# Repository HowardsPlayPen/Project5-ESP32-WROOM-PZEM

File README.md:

# Project 5: ESP32WROOM + some SMD soldering

So far, all my projects had involved modules for each component, such as using an ESP32-CAM, but I wanted to move to use more compact components - such as the ESP32-S2. The camera on the ESP32-CAM is amazing and simple to use - but for most of the projects I wanted to build having more GPIO pins available seemed like a better option.

At this point a friend sent me the following [link](https://twitter.com/i/status/1598419769077952512) showing an amazing PCB that was not much thicker than the PCB board but with a wonderul TFT screen built in

The twitter feed included a link to where you can buy the TFT on [AliExpress](https://www.aliexpress.com/item/1005003768946439.html)

Specs: 240*280 RGB Build-in ST7789 Driver Serial IPS Display

Note: this is **WAY** better than the SSD1306 I have been using which is a 0.96' screen 128x64 single colour screen

I wanted to try out these screens but I haven't soldered FPC cables before and so I bought several of these and one module that breaks out the wires into standard 2.54 mm pins. This way I could test the board to know it drives the panel ok before worrying about the FPC side

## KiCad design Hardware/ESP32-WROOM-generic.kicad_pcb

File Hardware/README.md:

# Project5-ESP32-WROOM

Using an ESP32-WROOM + RFM69HW + PZEM + pinouts for a few different LED screens.

## Aim

Test out various different circuits - including touch buttons connected to ESP32 pins (I read that they could work as capacitative buttons)

It includes a connector for PZEM - i.e. ability to monitor 240V power use.

### PZEM v3
I bought my PZEM from Aliexpress but they are available everywhere, eg. [see here](https://esphome.io/components/sensor/pzemac.html)

## NOTE about OLED screen / board

> Note: this board does not connect BLK to 3V as the documentation said it was optional. This PCB works for the ST7789V2 boards that I have, but does not work for a newer ST7789V3 board where it **NEEDS**  BLK to be connected to 3V.

### Kicad Rendering of the PCB

### Kicad view of the PCB

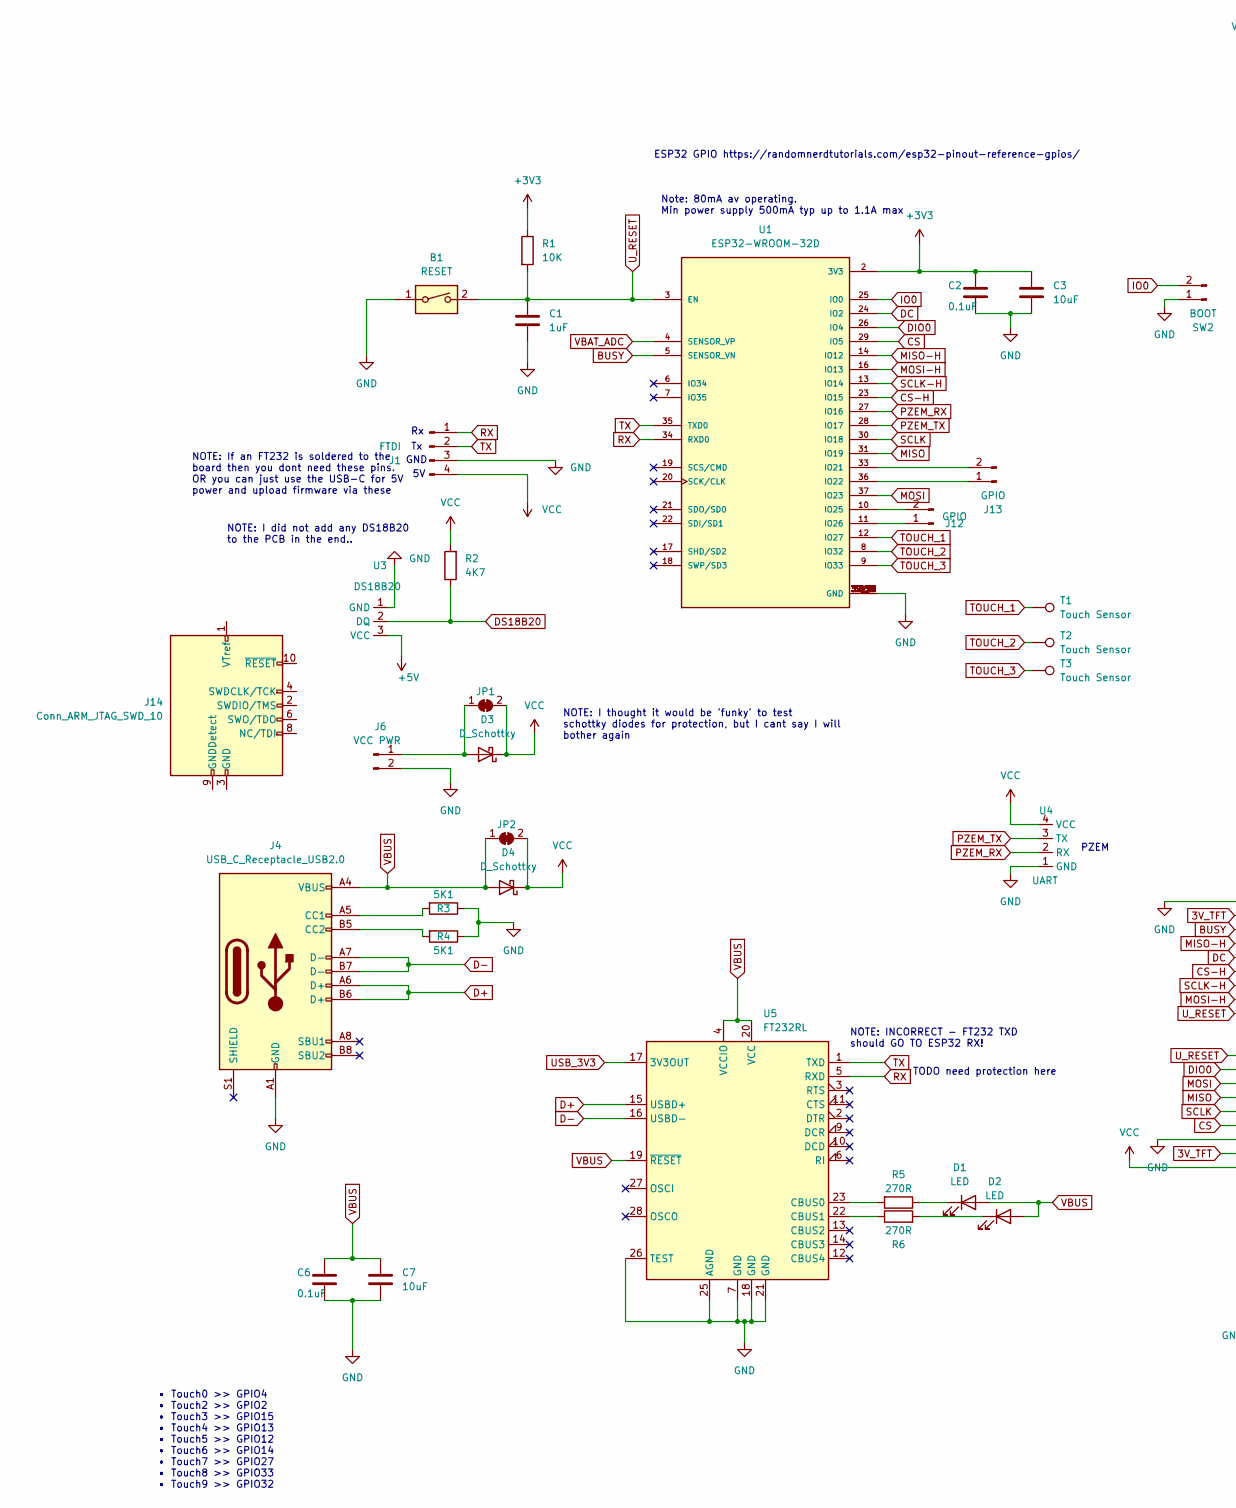
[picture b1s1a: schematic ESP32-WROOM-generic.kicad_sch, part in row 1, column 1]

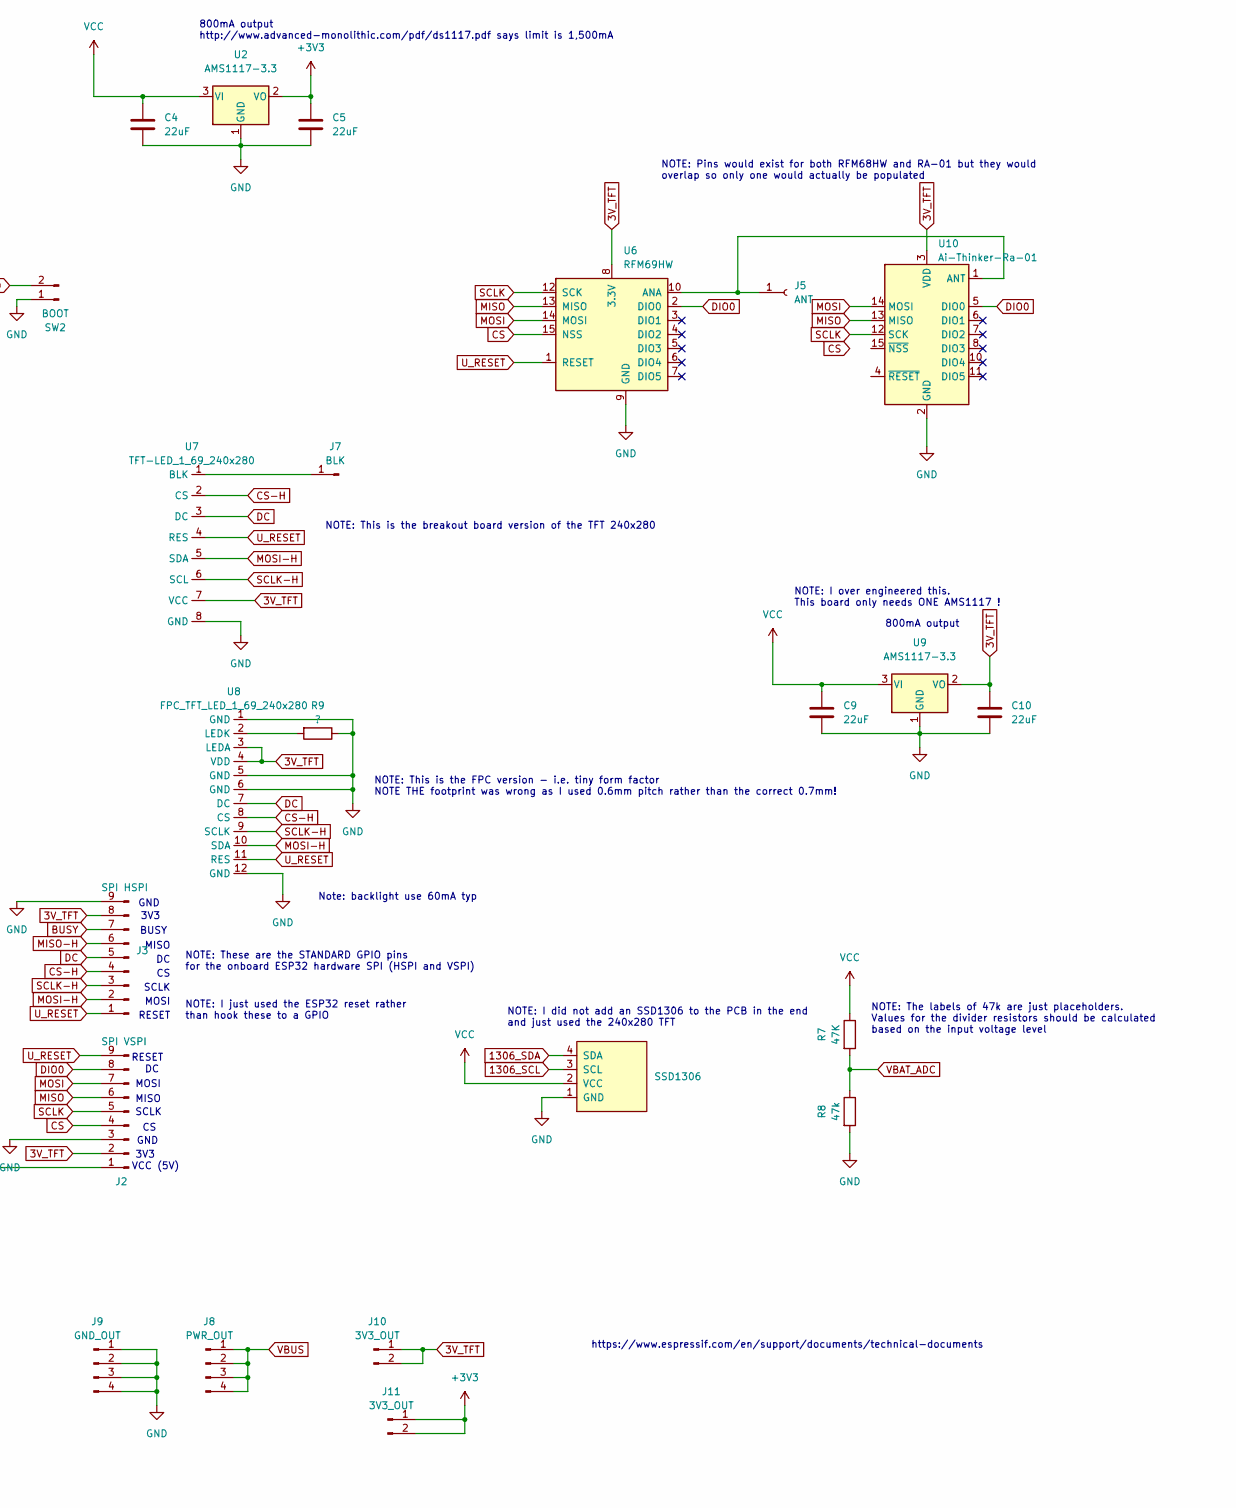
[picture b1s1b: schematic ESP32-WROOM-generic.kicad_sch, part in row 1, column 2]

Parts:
B1: RESET; SW_DIP_SPSTx01_Slide_6.7x4.1mm_W8.61mm_P2.54mm_LowProfile
Brd1: SSD1306; 128x64OLED
C1: 1uF; C_0504_1310Metric_Pad0.83x1.28mm_HandSolder
C2, C6: 0.1uF; C_0504_1310Metric_Pad0.83x1.28mm_HandSolder
C3, C7: 10uF; C_0504_1310Metric_Pad0.83x1.28mm_HandSolder
C4, C5, C9, C10: 22uF; C_0504_1310Metric_Pad0.83x1.28mm_HandSolder
D1, D2: LED; LED_1206_3216Metric_Pad1.42x1.75mm_HandSolder
D3, D4: D_Schottky; D_MELF
J1: FTDI; JST_EH_B4B-EH-A_1x04_P2.50mm_Vertical
J2: SPI VSPI; JST_EH_B9B-EH-A_1x09_P2.50mm_Vertical
J3: SPI HSPI; JST_EH_B9B-EH-A_1x09_P2.50mm_Vertical
J4: USB_C_Receptacle_USB2.0; USB_C_Receptacle_HRO_TYPE-C-31-M-12
J5: ANT; Pin_D1.0mm_L10.0mm
J6: VCC PWR; JST_EH_B2B-EH-A_1x02_P2.50mm_Vertical
J7: BLK; TestPoint_Plated_Hole_D2.0mm
J8: PWR_OUT; JST_EH_B4B-EH-A_1x04_P2.50mm_Vertical
J9: GND_OUT; JST_EH_B4B-EH-A_1x04_P2.50mm_Vertical
J10, J11: 3V3_OUT; JST_EH_B2B-EH-A_1x02_P2.50mm_Vertical
J12, J13: GPIO; JST_EH_B2B-EH-A_1x02_P2.50mm_Vertical
J14: Conn_ARM_JTAG_SWD_10
JP1, JP2: SolderJumper_2_Bridged; SolderJumper-2_P1.3mm_Bridged_Pad1.0x1.5mm
R1: 10K; R_1206_3216Metric_Pad1.30x1.75mm_HandSolder
R2: 4K7; R_1206_3216Metric_Pad1.30x1.75mm_HandSolder
R3, R4: 5K1; R_1206_3216Metric_Pad1.30x1.75mm_HandSolder
R5, R6: 270R; R_1206_3216Metric_Pad1.30x1.75mm_HandSolder
R7: 47K; R_1206_3216Metric_Pad1.30x1.75mm_HandSolder
R8: 47k; R_1206_3216Metric_Pad1.30x1.75mm_HandSolder
R9: ?; R_1206_3216Metric_Pad1.30x1.75mm_HandSolder
SW2: BOOT; JST_EH_B2B-EH-A_1x02_P2.50mm_Vertical
T1, T2, T3: Touch Sensor; TestPoint_Pad_D4.0mm
U1: ESP32-WROOM-32D; MODULE_ESP32-WROOM-32D; PARTREV 1.9
U2, U9: AMS1117-3.3; SOT-223-3_TabPin2
U3: DS18B20; JST_NV_B03P-NV_1x03_P5.00mm_Vertical
U4: UART; JST_EH_B4B-EH-A_1x04_P2.50mm_Vertical
U5: FT232RL; SSOP-28_5.3x10.2mm_P0.65mm
U6: RFM69HW; HOPERF_RFM69HW
U7: TFT-LED_1_69_240x280
U8: FPC_TFT_LED_1_69_240x280; FPC_TFT_1_69_240x280
U10: Ai-Thinker-Ra-01; Ai-Thinker-Ra-01-LoRa

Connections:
3V_TFT: C10.1, J2.2, J3.8, J10.1, J10.2, U6.8 (3.3V), U7.7 (VCC), U8.3 (LEDA), U8.4 (VDD), U9.2 (VO), U10.3 (VDD)
+3V3: C2.1, C3.1, C5.1, J11.1, J11.2, R1.1, U1.2 (3V3), U2.2 (VO)
BUSY: J3.7, U1.5 (SENSOR_VN)
CS: J2.4, U1.29 (IO5), U6.15 (NSS)
CS-H: J3.4, U1.23 (IO15), U7.2 (CS), U8.8 (CS)
D+: J4.A6 (D+), J4.B6 (D+), U5.15 (USBD+)
D-: J4.A7 (D-), J4.B7 (D-), U5.16 (USBD-)
DC: J3.5, U1.24 (IO2), U7.3 (DC), U8.7 (DC)
DIO0: J2.8, U1.26 (IO4), U6.2 (DIO0), U10.5 (DIO0)
GND: B1.1, Brd1.1 (GND), C1.2, C2.2, C3.2, C4.2, C5.2, C6.2, C7.2, C9.2, C10.2, J1.3, J2.3, J3.9, J4.A1 (GND), J4.A12 (GND), J4.B1 (GND), J4.B12 (GND), J6.2, J9.1, J9.2, J9.3, J9.4, R3.1, R4.1, R8.2, R9.1, SW2.1, U1.1 (GND), U1.15 (GND), U1.38 (GND), U1.39_1 (GND), U1.39_2 (GND), U1.39_3 (GND), U1.39_4 (GND), U1.39_5 (GND), U1.39_6 (GND), U1.39_7 (GND), U1.39_8 (GND), U1.39_9 (GND), U1.39_10 (GND), U1.39_11 (GND), U1.39_12 (GND), U1.39_13 (GND), U1.39_14 (GND), U1.39_15 (GND), U1.39_16 (GND), U1.39_17 (GND), U1.39_18 (GND), U1.39_19 (GND), U1.39_20 (GND), U1.39_21 (GND), U2.1 (GND), U3.1 (GND), U4.1 (GND), U5.7 (GND), U5.18 (GND), U5.21 (GND), U5.25 (AGND), U5.26 (TEST), U6.9 (GND), U6.11 (GND), U7.8 (GND), U8.1 (GND), U8.5 (GND), U8.6 (GND), U8.12 (GND), U9.1 (GND), U10.2 (GND), U10.9 (GND), U10.16 (GND); also elsewhere on the board
IO0: SW2.2, U1.25 (IO0)
MISO: J2.6, U1.31 (IO19), U6.13 (MISO), U10.13 (MISO)
MISO-H: J3.6, U1.14 (IO12)
MOSI: J2.7, U1.37 (IO23), U6.14 (MOSI), U10.14 (MOSI)
MOSI-H: J3.2, U1.16 (IO13), U7.5 (SDA), U8.10 (SDA)
unnamed: D1.1 (K), R5.1
unnamed: D2.1 (K), R6.2
unnamed: D3.2 (A), J6.1, JP1.1 (A)
unnamed: J4.A5 (CC1), R3.2
unnamed: J4.B5 (CC2), R4.2
unnamed: J5.1, U6.10 (ANA), U10.1 (ANT)
unnamed: J7.1, U7.1 (BLK)
unnamed: J12.1, U1.11 (IO26)
unnamed: J12.2, U1.10 (IO25)
unnamed: J13.1, U1.36 (IO22)
unnamed: J13.2, U1.33 (IO21)
unnamed: J14.3 (GND), J14.5 (GND)
unnamed: R2.1, U3.2 (DQ)
unnamed: R5.2, U5.23 (CBUS0)
unnamed: R6.1, U5.22 (CBUS1)
unnamed: R9.2, U8.2 (LEDK)
PZEM_RX: U1.27 (IO16), U4.2 (RX)
PZEM_TX: U1.28 (IO17), U4.3 (TX)
RX: J1.1, U1.34 (RXD0), U5.5 (RXD)
SCLK: J2.5, U1.30 (IO18), U6.12 (SCK), U10.12 (SCK)
SCLK-H: J3.3, U1.13 (IO14), U7.6 (SCL), U8.9 (SCLK)
TOUCH_1: T1.1, U1.12 (IO27)
TOUCH_2: T2.1, U1.8 (IO32)
TOUCH_3: T3.1, U1.9 (IO33)
TX: J1.2, U1.35 (TXD0), U5.1 (TXD)
USB_3V3: U5.17 (3V3OUT)
U_RESET: B1.2, C1.1, J2.9, J3.1, R1.2, U1.3 (EN), U6.1 (RESET), U7.4 (RES), U8.11 (RES)
VBAT_ADC: R7.2, R8.1, U1.4 (SENSOR_VP)
VBUS: C6.1, C7.1, D1.2 (A), D2.2 (A), D4.2 (A), J4.A4 (VBUS), J4.A9 (VBUS), J4.B4 (VBUS), J4.B9 (VBUS), J8.1, J8.2, J8.3, J8.4, JP2.1 (A), U5.4 (VCCIO), U5.19 (~RESET), U5.20 (VCC); also elsewhere on the board
VCC: Brd1.2 (VCC), C4.1, C9.1, D3.1 (K), D4.1 (K), J1.4, J2.1, JP1.2 (B), JP2.2 (B), R2.2, R7.1, U2.3 (VI), U4.4 (VCC), U9.3 (VI)

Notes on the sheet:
RESET
NOTE: I over engineered this. This board only needs ONE AMS1117 !
Note: backlight use 60mA typ
NOTE: If an FT232 is soldered to the board then you dont need these pins. OR you can just use the USB-C for 5V power and upload firmware via these
NOTE: This is the FPC version - i.e. tiny form factor NOTE THE footprint was wrong as I used 0.6mm pitch rather than the correct 0.7mm!
NOTE: The labels of 47k are just placeholders. Values for the divider resistors should be calculated based on the input voltage level
NOTE: These are the STANDARD GPIO pins for the onboard ESP32 hardware SPI (HSPI and VSPI)
NOTE: I did not add any DS18B20 to the PCB in the end..
VCC (5V)
MOSI
ESP32 GPIO https://randomnerdtutorials.com/esp32-pinout-reference-gpios/
• Touch0 >> GPIO4 • Touch2 >> GPIO2 • Touch3 >> GPIO15 • Touch4 >> GPIO13 • Touch5 >> GPIO12 • Touch6 >> GPIO14 • Touch7 >> GPIO27 • Touch8 >> GPIO33 • Touch9 >> GPIO32
MISO
800mA output http://www.advanced-monolithic.com/pdf/ds1117.pdf says limit is 1,500mA
GND
3V3
TODO need protection here
NOTE: I thought it would be 'funky' to test schottky diodes for protection, but I cant say I will bother again
NOTE: Pins would exist for both RFM68HW and RA-01 but they would overlap so only one would actually be populated
800mA output
SCLK
NOTE: I did not add an SSD1306 to the PCB in the end and just used the 240x280 TFT
NOTE: INCORRECT - FT232 TXD should GO TO ESP32 RX!
NOTE: This is the breakout board version of the TFT 240x280
PZEM
Note: 80mA av operating. Min power supply 500mA typ up to 1.1A max
https://www.espressif.com/en/support/documents/technical-documents
NOTE: I just used the ESP32 reset rather than hook these to a GPIO
BUSY

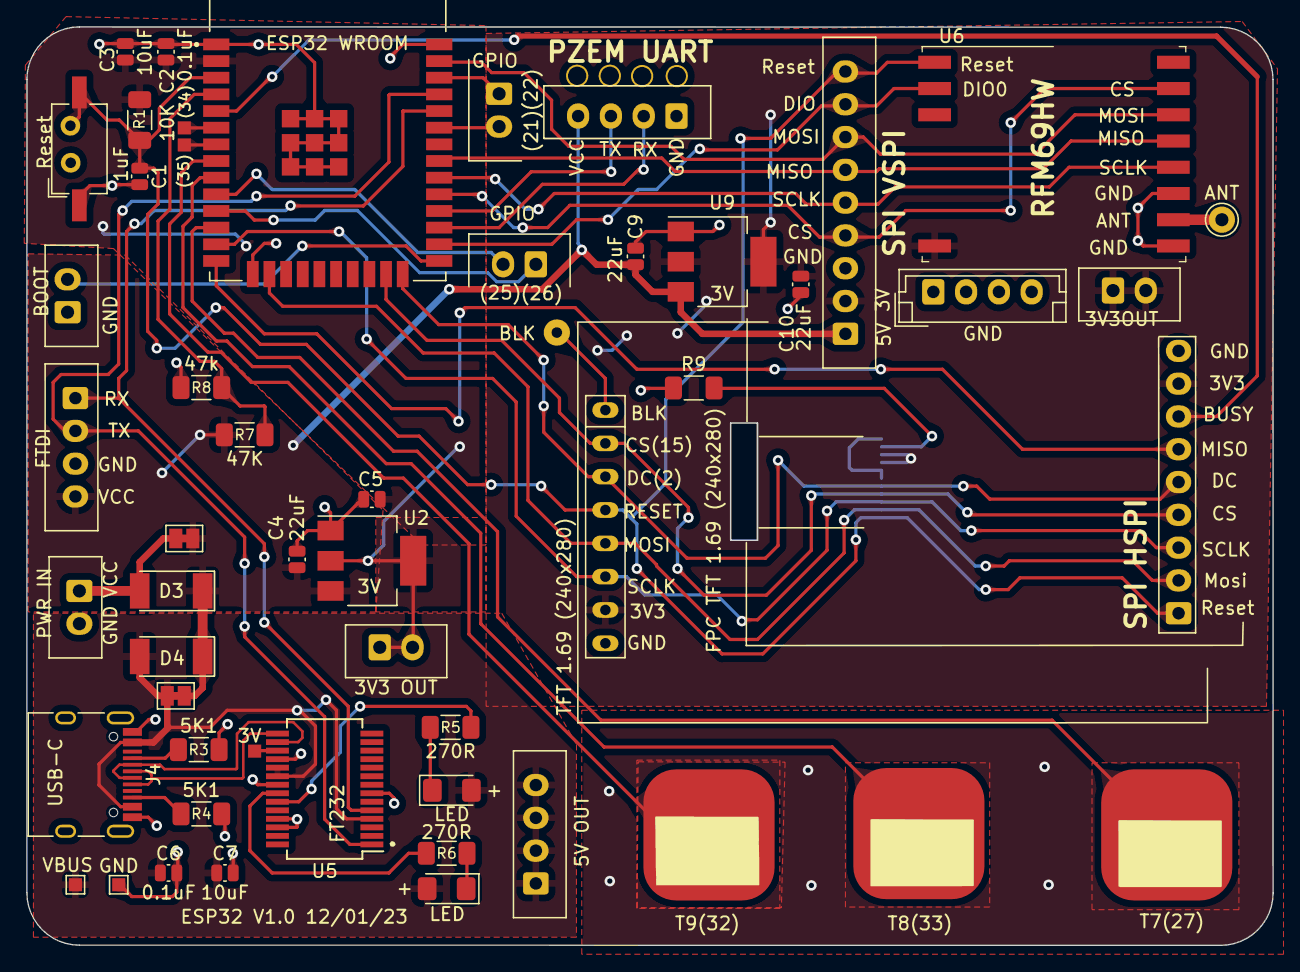
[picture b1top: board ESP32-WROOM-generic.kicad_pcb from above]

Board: 2 copper layers, 95.0 x 70.0 mm, 51 parts (0 on the bottom side), 42 nets.

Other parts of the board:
GND: TestPoint_Pad_1.0x1.0mm
VBUS: TestPoint_Pad_1.0x1.0mm

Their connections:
GND: GND.1; also elsewhere on the board
VBUS: VBUS.1; also elsewhere on the board

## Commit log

2025-05-28 Tweak to README
2025-05-28 Removed unecessary files
2025-05-28 Tweaks to readme
2025-05-28 Tweak
